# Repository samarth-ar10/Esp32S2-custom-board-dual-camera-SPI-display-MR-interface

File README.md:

# Esp32S2-custom-board-dual-camera-SPI-display-MR-interface

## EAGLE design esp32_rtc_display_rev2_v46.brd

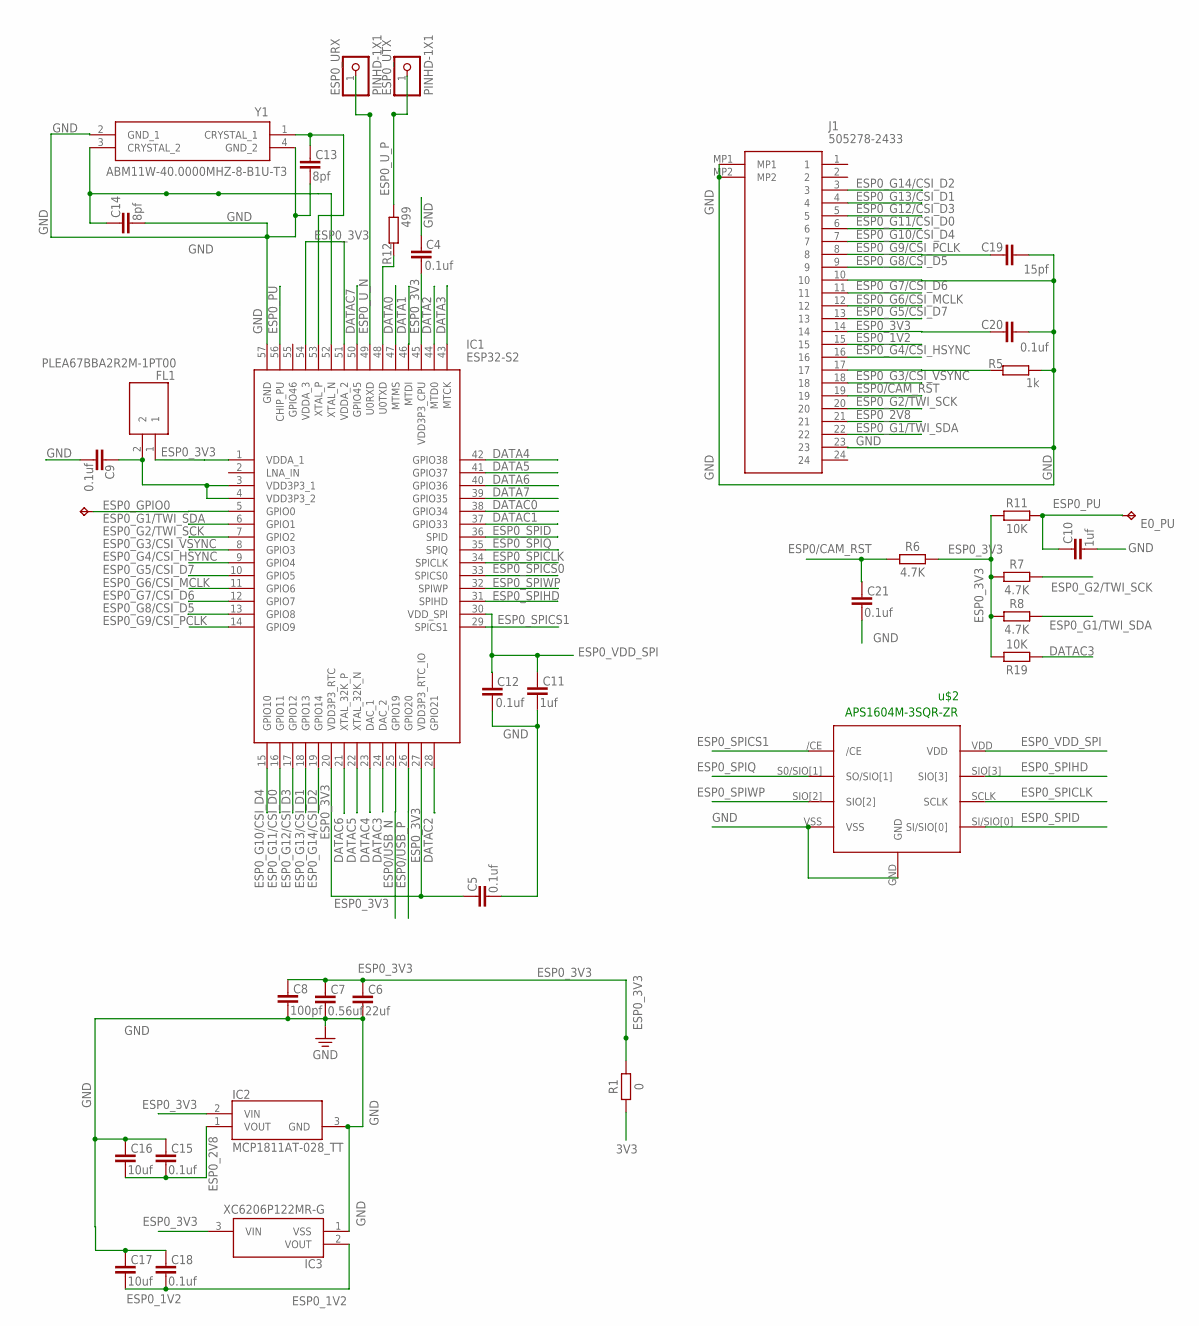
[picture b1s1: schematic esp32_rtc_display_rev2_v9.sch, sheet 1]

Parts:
C4, C5, C9, C12, C15, C18, C20, C21: 0.1uf; CAPC1005X60
C6: 22uf; CAPC1005X60
C7: 0.56uf; CAPC1005X60
C8: 100pf; CAPC1005X60
C10, C11: 1uf; CAPC1005X60
C13, C14: 8pf; CAPC1005X60
C16, C17: 10uf; CAPC1005X60
C19: 15pf; CAPC1005X60
E0_G0, E0_PU: TPTP10R; TP10R
ESP0_URX, ESP0_UTX: PINHD-1X1; 1X01
FL1: PLEA67BBA2R2M-1PT00; PLEA67BBA2R2M1PT00
IC1: ESP32-S2; QFN40P700X700X90-57N
IC2: MCP1811AT-028_TT; SOT65P210X110-3N
IC3: XC6206P122MR-G; SOT95P280X130-3N
J1: 505278-2433; 5052782433
R1: 0; RESC1005X40
R5: 1k; RESC1005X40
R6, R7, R8: 4.7K; RESC1005X40
R11, R19: 10K; RESC1005X40
R12: 499; RESC1005X40
U$2: APS1604M-3SQR-ZR
Y1: ABM11W-40.0000MHZ-8-B1U-T3; ABM11W400000MHZ8B1UT3

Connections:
3V3: R1.2; also elsewhere on the board
DATA0: IC1.47 (MTMS); also elsewhere on the board
DATA1: IC1.46 (MTDI); also elsewhere on the board
DATA2: IC1.44 (MTD0); also elsewhere on the board
DATA3: IC1.43 (MTCK); also elsewhere on the board
DATA4: IC1.42 (GPIO38); also elsewhere on the board
DATA5: IC1.41 (GPIO37); also elsewhere on the board
DATA6: IC1.40 (GPIO36); also elsewhere on the board
DATA7: IC1.39 (GPIO35); also elsewhere on the board
DATAC0: IC1.38 (GPIO34); also elsewhere on the board
DATAC1: IC1.37 (GPIO33); also elsewhere on the board
DATAC2: IC1.28 (GPIO21); also elsewhere on the board
DATAC3: IC1.24 (DAC_2), R19.2; also elsewhere on the board
DATAC4: IC1.23 (DAC_1); also elsewhere on the board
DATAC5: IC1.22 (XTAL_32K_N); also elsewhere on the board
DATAC6: IC1.21 (XTAL_32K_P); also elsewhere on the board
DATAC7: IC1.50 (GPIO45); also elsewhere on the board
ESP0/CAM_RST: C21.1, J1.19, R6.1
ESP0/USB_N: IC1.25 (GPIO19); also elsewhere on the board
ESP0/USB_P: IC1.26 (GPIO20); also elsewhere on the board
ESP0_1V2: C17.2, C18.2, IC3.2 (VOUT), J1.15
ESP0_2V8: C15.2, C16.2, IC2.1 (VOUT), J1.21
ESP0_3V3: C4.2, C5.1, C6.1, C7.1, C8.1, C20.1, FL1.1, IC1.1 (VDDA_1), IC1.20 (VDD3P3_RTC), IC1.27 (VDD3P3_RTC_IO), IC1.45 (VDD3P3_CPU), IC1.51 (VDDA_2), IC1.54 (VDDA_3), IC2.2 (VIN), IC3.3 (VIN), J1.14, R1.1, R6.2, R7.2, R8.2, R11.2, R19.1
ESP0_G1/TWI_SDA: IC1.6 (GPIO1), J1.22, R8.1
ESP0_G2/TWI_SCK: IC1.7 (GPIO2), J1.20, R7.1
ESP0_G3/CSI_VSYNC: IC1.8 (GPIO3), J1.18
ESP0_G4/CSI_HSYNC: IC1.9 (GPIO4), J1.16
ESP0_G5/CSI_D7: IC1.10 (GPIO5), J1.13
ESP0_G6/CSI_MCLK: IC1.11 (GPIO6), J1.12
ESP0_G7/CSI_D6: IC1.12 (GPIO7), J1.11
ESP0_G8/CSI_D5: IC1.13 (GPIO8), J1.9
ESP0_G9/CSI_PCLK: C19.1, IC1.14 (GPIO9), J1.8
ESP0_G10/CSI_D4: IC1.15 (GPIO10), J1.7
ESP0_G11/CSI_D0: IC1.16 (GPIO11), J1.6
ESP0_G12/CSI_D3: IC1.17 (GPIO12), J1.5
ESP0_G13/CSI_D1: IC1.18 (GPIO13), J1.4
ESP0_G14/CSI_D2: IC1.19 (GPIO14), J1.3
ESP0_GPIO0: E0_G0.TP, IC1.5 (GPIO0); also elsewhere on the board
ESP0_PU: C10.1, E0_PU.TP, IC1.56 (CHIP_PU), R11.1; also elsewhere on the board
ESP0_SPICLK: IC1.34 (SPICLK), U$2.SCLK
ESP0_SPICS0: IC1.33 (SPICS0)
ESP0_SPICS1: IC1.29 (SPICS1), U$2./CE
ESP0_SPID: IC1.36 (SPID), U$2.SI/SIO[0]
ESP0_SPIHD: IC1.31 (SPIHD), U$2.SIO[3]
ESP0_SPIQ: IC1.35 (SPIQ), U$2.S0/SIO[1] (SO/SIO[1])
ESP0_SPIWP: IC1.32 (SPIWP), U$2.SIO[2]
ESP0_U_N: ESP0_URX.1, IC1.49 (U0RXD); also elsewhere on the board
ESP0_U_P: ESP0_UTX.1, R12.2; also elsewhere on the board
ESP0_VDD_SPI: C11.1, C12.1, IC1.30 (VDD_SPI), U$2.VDD
GND: C4.1, C5.2, C6.2, C7.2, C8.2, C9.2, C10.2, C11.2, C12.2, C13.2, C14.2, C15.1, C16.1, C17.1, C18.1, C19.2, C20.2, C21.2, IC1.57 (GND), IC2.3 (GND), IC3.1 (VSS), J1.10, J1.23, J1.MP1, J1.MP2, R5.2, U$2.GND, U$2.VSS, Y1.2 (GND_1), Y1.4 (GND_2); also elsewhere on the board
unnamed: C13.1, IC1.53 (XTAL_P), Y1.1 (CRYSTAL_1)
unnamed: IC1.48 (U0TXD), R12.1
unnamed: C14.1, IC1.52 (XTAL_N), Y1.3 (CRYSTAL_2)
unnamed: J1.17, R5.1
unnamed: C9.1, FL1.2, IC1.3 (VDD3P3_1), IC1.4 (VDD3P3_2)

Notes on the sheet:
APS1604M-3SQR-ZR
u$2

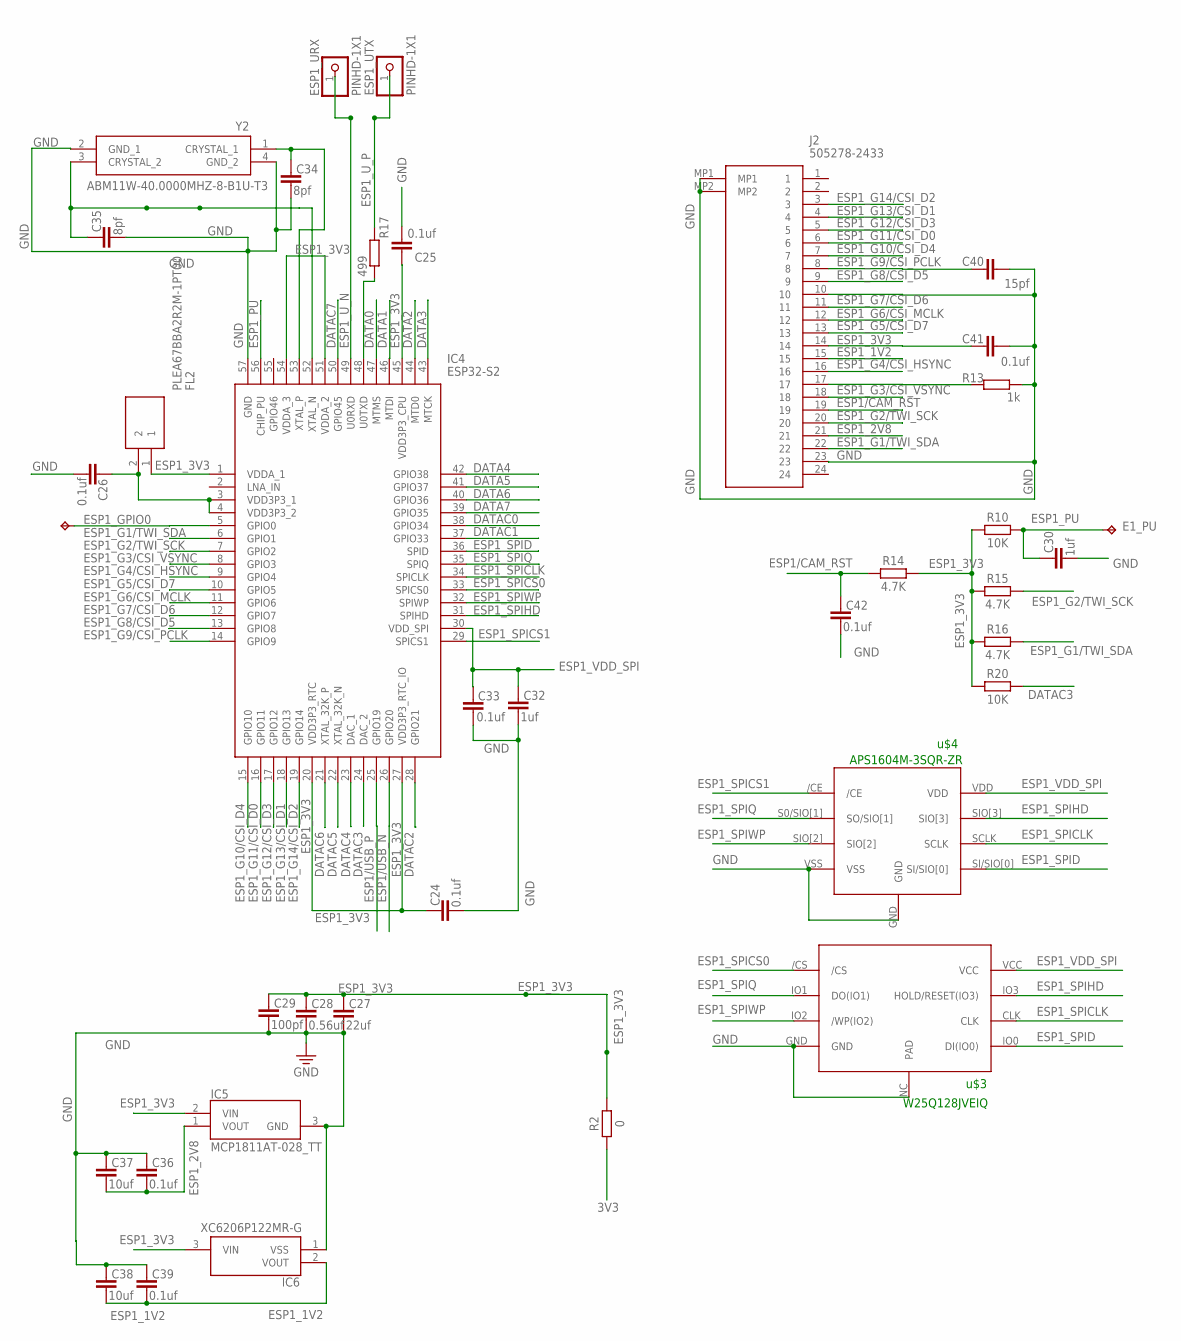
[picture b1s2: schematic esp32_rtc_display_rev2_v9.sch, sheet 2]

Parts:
C24, C25, C26, C33, C36, C39, C41, C42: 0.1uf; CAPC1005X60
C27: 22uf; CAPC1005X60
C28: 0.56uf; CAPC1005X60
C29: 100pf; CAPC1005X60
C30, C32: 1uf; CAPC1005X60
C34, C35: 8pf; CAPC1005X60
C37, C38: 10uf; CAPC1005X60
C40: 15pf; CAPC1005X60
E1_G0, E1_PU: TPTP10R; TP10R
ESP1_URX, ESP1_UTX: PINHD-1X1; 1X01
FL2: PLEA67BBA2R2M-1PT00; PLEA67BBA2R2M1PT00
IC4: ESP32-S2; QFN40P700X700X90-57N
IC5: MCP1811AT-028_TT; SOT65P210X110-3N
IC6: XC6206P122MR-G; SOT95P280X130-3N
J2: 505278-2433; 5052782433
R2: 0; RESC1005X40
R10, R20: 10K; RESC1005X40
R13: 1k; RESC1005X40
R14, R15, R16: 4.7K; RESC1005X40
R17: 499; RESC1005X40
U$3: W25Q128JVEIQ
U$4: APS1604M-3SQR-ZR
Y2: ABM11W-40.0000MHZ-8-B1U-T3; ABM11W400000MHZ8B1UT3

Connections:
3V3: R2.2; also elsewhere on the board
DATA0: IC4.47 (MTMS); also elsewhere on the board
DATA1: IC4.46 (MTDI); also elsewhere on the board
DATA2: IC4.44 (MTD0); also elsewhere on the board
DATA3: IC4.43 (MTCK); also elsewhere on the board
DATA4: IC4.42 (GPIO38); also elsewhere on the board
DATA5: IC4.41 (GPIO37); also elsewhere on the board
DATA6: IC4.40 (GPIO36); also elsewhere on the board
DATA7: IC4.39 (GPIO35); also elsewhere on the board
DATAC0: IC4.38 (GPIO34); also elsewhere on the board
DATAC1: IC4.37 (GPIO33); also elsewhere on the board
DATAC2: IC4.28 (GPIO21); also elsewhere on the board
DATAC3: IC4.24 (DAC_2), R20.1; also elsewhere on the board
DATAC4: IC4.23 (DAC_1); also elsewhere on the board
DATAC5: IC4.22 (XTAL_32K_N); also elsewhere on the board
DATAC6: IC4.21 (XTAL_32K_P); also elsewhere on the board
DATAC7: IC4.50 (GPIO45); also elsewhere on the board
ESP1/CAM_RST: C42.1, J2.19, R14.1
ESP1/USB_N: IC4.26 (GPIO20); also elsewhere on the board
ESP1/USB_P: IC4.25 (GPIO19); also elsewhere on the board
ESP1_1V2: C38.2, C39.2, IC6.2 (VOUT), J2.15
ESP1_2V8: C36.2, C37.2, IC5.1 (VOUT), J2.21
ESP1_3V3: C24.1, C25.1, C27.1, C28.1, C29.1, C41.1, FL2.1, IC4.1 (VDDA_1), IC4.20 (VDD3P3_RTC), IC4.27 (VDD3P3_RTC_IO), IC4.45 (VDD3P3_CPU), IC4.51 (VDDA_2), IC4.54 (VDDA_3), IC5.2 (VIN), IC6.3 (VIN), J2.14, R2.1, R10.2, R14.2, R15.2, R16.2, R20.2
ESP1_G1/TWI_SDA: IC4.6 (GPIO1), J2.22, R16.1
ESP1_G2/TWI_SCK: IC4.7 (GPIO2), J2.20, R15.1
ESP1_G3/CSI_VSYNC: IC4.8 (GPIO3), J2.18
ESP1_G4/CSI_HSYNC: IC4.9 (GPIO4), J2.16
ESP1_G5/CSI_D7: IC4.10 (GPIO5), J2.13
ESP1_G6/CSI_MCLK: IC4.11 (GPIO6), J2.12
ESP1_G7/CSI_D6: IC4.12 (GPIO7), J2.11
ESP1_G8/CSI_D5: IC4.13 (GPIO8), J2.9
ESP1_G9/CSI_PCLK: C40.1, IC4.14 (GPIO9), J2.8
ESP1_G10/CSI_D4: IC4.15 (GPIO10), J2.7
ESP1_G11/CSI_D0: IC4.16 (GPIO11), J2.6
ESP1_G12/CSI_D3: IC4.17 (GPIO12), J2.5
ESP1_G13/CSI_D1: IC4.18 (GPIO13), J2.4
ESP1_G14/CSI_D2: IC4.19 (GPIO14), J2.3
ESP1_GPIO0: E1_G0.TP, IC4.5 (GPIO0); also elsewhere on the board
ESP1_PU: C30.1, E1_PU.TP, IC4.56 (CHIP_PU), R10.1; also elsewhere on the board
ESP1_SPICLK: IC4.34 (SPICLK), U$3.CLK, U$4.SCLK
ESP1_SPICS0: IC4.33 (SPICS0), U$3./CS
ESP1_SPICS1: IC4.29 (SPICS1), U$4./CE
ESP1_SPID: IC4.36 (SPID), U$3.IO0 (DI(IO0)), U$4.SI/SIO[0]
ESP1_SPIHD: IC4.31 (SPIHD), U$3.IO3 (HOLD/RESET(IO3)), U$4.SIO[3]
ESP1_SPIQ: IC4.35 (SPIQ), U$3.IO1 (DO(IO1)), U$4.S0/SIO[1] (SO/SIO[1])
ESP1_SPIWP: IC4.32 (SPIWP), U$3.IO2 (/WP(IO2)), U$4.SIO[2]
ESP1_U_N: ESP1_URX.1, IC4.49 (U0RXD); also elsewhere on the board
ESP1_U_P: ESP1_UTX.1, R17.1; also elsewhere on the board
ESP1_VDD_SPI: C32.1, C33.1, IC4.30 (VDD_SPI), U$3.VCC, U$4.VDD
GND: C24.2, C25.2, C26.2, C27.2, C28.2, C29.2, C30.2, C32.2, C33.2, C34.2, C35.2, C36.1, C37.1, C38.1, C39.1, C40.2, C41.2, C42.2, IC4.57 (GND), IC5.3 (GND), IC6.1 (VSS), J2.10, J2.23, J2.MP1, J2.MP2, R13.2, U$3.GND, U$3.NC (PAD), U$4.GND, U$4.VSS, Y2.2 (GND_1), Y2.4 (GND_2); also elsewhere on the board
unnamed: IC4.48 (U0TXD), R17.2
unnamed: C35.1, IC4.52 (XTAL_N), Y2.3 (CRYSTAL_2)
unnamed: C34.1, IC4.53 (XTAL_P), Y2.1 (CRYSTAL_1)
unnamed: J2.17, R13.1
unnamed: C26.1, FL2.2, IC4.3 (VDD3P3_1), IC4.4 (VDD3P3_2)

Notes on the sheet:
APS1604M-3SQR-ZR
u$4
W25Q128JVEIQ
u$3

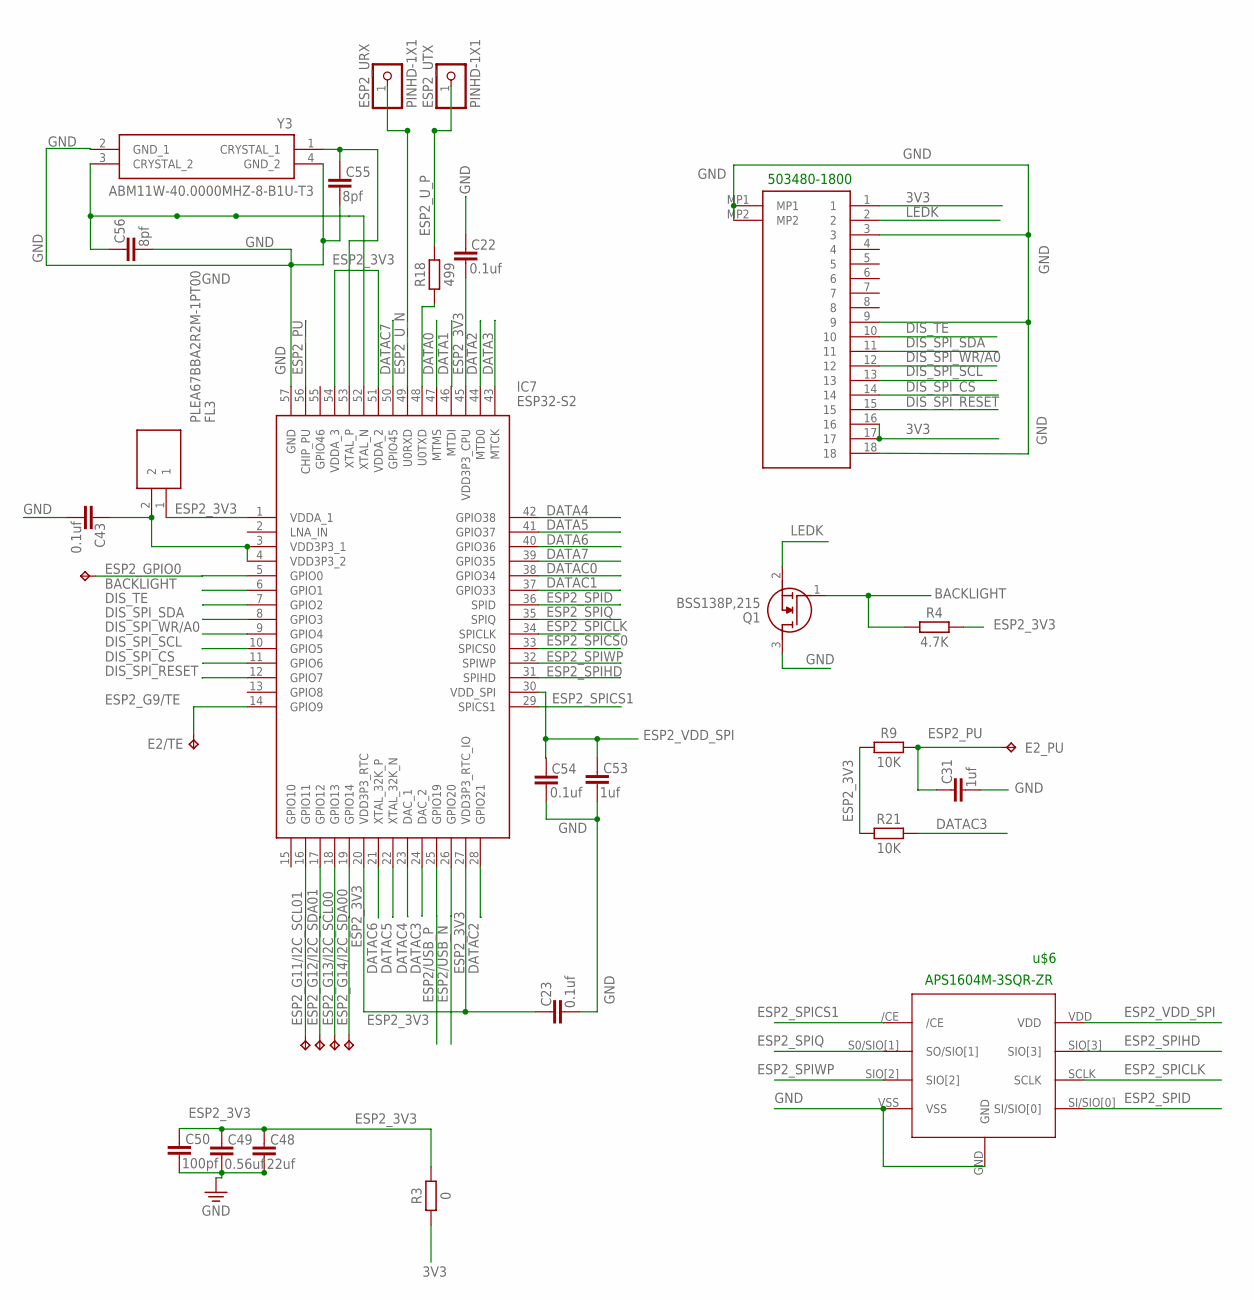
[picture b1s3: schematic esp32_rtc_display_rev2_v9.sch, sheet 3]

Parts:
C22, C23, C43, C54: 0.1uf; CAPC1005X60
C31, C53: 1uf; CAPC1005X60
C48: 22uf; CAPC1005X60
C49: 0.56uf; CAPC1005X60
C50: 100pf; CAPC1005X60
C55, C56: 8pf; CAPC1005X60
E2/TE, E2_G0, E2_PU: TPTP10R; TP10R
ESP2_URX, ESP2_UTX: PINHD-1X1; 1X01
FL3: PLEA67BBA2R2M-1PT00; PLEA67BBA2R2M1PT00
IC7: ESP32-S2; QFN40P700X700X90-57N
Q1: BSS138P,215; SOT95P230X110-3N
R3: 0; RESC1005X40
R4: 4.7K; RESC1005X40
R9, R21: 10K; RESC1005X40
R18: 499; RESC1005X40
SCL00, SCL01: TPTP10R; TP10R
SDA00, SDA01: TPTP10R; TP10R
U$5: 503480-1800; 5034801800
U$6: APS1604M-3SQR-ZR
Y3: ABM11W-40.0000MHZ-8-B1U-T3; ABM11W400000MHZ8B1UT3

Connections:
3V3: R3.2, U$5.1, U$5.16, U$5.17; also elsewhere on the board
BACKLIGHT: IC7.6 (GPIO1), Q1.1 (G), R4.1
DATA0: IC7.47 (MTMS); also elsewhere on the board
DATA1: IC7.46 (MTDI); also elsewhere on the board
DATA2: IC7.44 (MTD0); also elsewhere on the board
DATA3: IC7.43 (MTCK); also elsewhere on the board
DATA4: IC7.42 (GPIO38); also elsewhere on the board
DATA5: IC7.41 (GPIO37); also elsewhere on the board
DATA6: IC7.40 (GPIO36); also elsewhere on the board
DATA7: IC7.39 (GPIO35); also elsewhere on the board
DATAC0: IC7.38 (GPIO34); also elsewhere on the board
DATAC1: IC7.37 (GPIO33); also elsewhere on the board
DATAC2: IC7.28 (GPIO21); also elsewhere on the board
DATAC3: IC7.24 (DAC_2), R21.1; also elsewhere on the board
DATAC4: IC7.23 (DAC_1); also elsewhere on the board
DATAC5: IC7.22 (XTAL_32K_N); also elsewhere on the board
DATAC6: IC7.21 (XTAL_32K_P); also elsewhere on the board
DATAC7: IC7.50 (GPIO45); also elsewhere on the board
DIS_SPI_CS: IC7.11 (GPIO6), U$5.14
DIS_SPI_RESET: IC7.12 (GPIO7), U$5.15
DIS_SPI_SCL: IC7.10 (GPIO5), U$5.13
DIS_SPI_SDA: IC7.8 (GPIO3), U$5.11
DIS_SPI_WR/A0: IC7.9 (GPIO4), U$5.12
DIS_TE: IC7.7 (GPIO2), U$5.10
ESP2/USB_N: IC7.26 (GPIO20); also elsewhere on the board
ESP2/USB_P: IC7.25 (GPIO19); also elsewhere on the board
ESP2_3V3: C22.2, C23.1, C48.1, C49.1, C50.1, FL3.1, IC7.1 (VDDA_1), IC7.20 (VDD3P3_RTC), IC7.27 (VDD3P3_RTC_IO), IC7.45 (VDD3P3_CPU), IC7.51 (VDDA_2), IC7.54 (VDDA_3), R3.1, R4.2, R9.2, R21.2
ESP2_G9/TE: E2/TE.TP, IC7.14 (GPIO9)
ESP2_G11/I2C_SCL01: IC7.16 (GPIO11), SCL01.TP
ESP2_G12/I2C_SDA01: IC7.17 (GPIO12), SDA01.TP
ESP2_G13/I2C_SCL00: IC7.18 (GPIO13), SCL00.TP
ESP2_G14/I2C_SDA00: IC7.19 (GPIO14), SDA00.TP
ESP2_GPIO0: E2_G0.TP, IC7.5 (GPIO0); also elsewhere on the board
ESP2_PU: C31.1, E2_PU.TP, IC7.56 (CHIP_PU), R9.1; also elsewhere on the board
ESP2_SPICLK: IC7.34 (SPICLK), U$6.SCLK
ESP2_SPICS0: IC7.33 (SPICS0)
ESP2_SPICS1: IC7.29 (SPICS1), U$6./CE
ESP2_SPID: IC7.36 (SPID), U$6.SI/SIO[0]
ESP2_SPIHD: IC7.31 (SPIHD), U$6.SIO[3]
ESP2_SPIQ: IC7.35 (SPIQ), U$6.S0/SIO[1] (SO/SIO[1])
ESP2_SPIWP: IC7.32 (SPIWP), U$6.SIO[2]
ESP2_U_N: ESP2_URX.1, IC7.49 (U0RXD); also elsewhere on the board
ESP2_U_P: ESP2_UTX.1, R18.2; also elsewhere on the board
ESP2_VDD_SPI: C53.1, C54.1, IC7.30 (VDD_SPI), U$6.VDD
GND: C22.1, C23.2, C31.2, C43.2, C48.2, C49.2, C50.2, C53.2, C54.2, C55.2, C56.2, IC7.57 (GND), Q1.3 (D), U$5.3, U$5.9, U$5.18, U$5.MP1, U$5.MP2, U$6.GND, U$6.VSS, Y3.2 (GND_1), Y3.4 (GND_2); also elsewhere on the board
LEDK: Q1.2 (S), U$5.2
unnamed: C56.1, IC7.52 (XTAL_N), Y3.3 (CRYSTAL_2)
unnamed: C55.1, IC7.53 (XTAL_P), Y3.1 (CRYSTAL_1)
unnamed: IC7.48 (U0TXD), R18.1
unnamed: C43.1, FL3.2, IC7.3 (VDD3P3_1), IC7.4 (VDD3P3_2)

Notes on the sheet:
APS1604M-3SQR-ZR
u$6
503480-1800

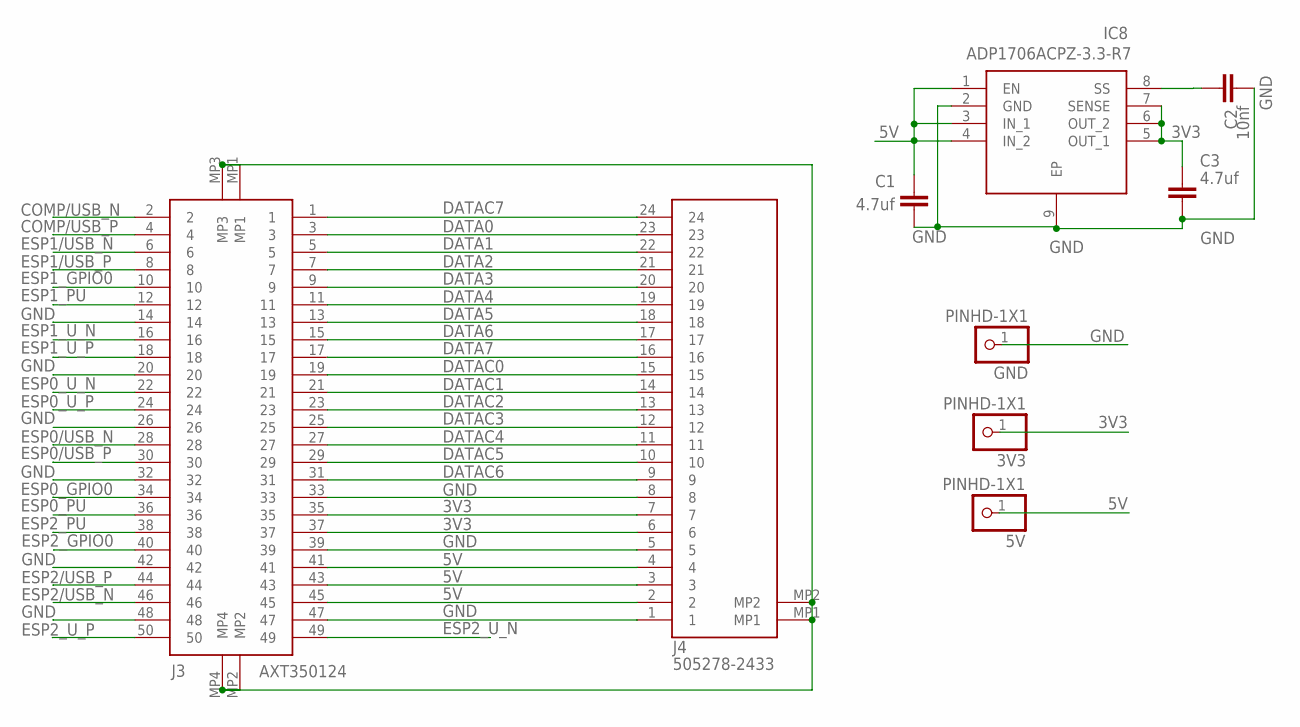
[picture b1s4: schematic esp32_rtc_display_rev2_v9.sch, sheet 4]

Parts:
3V3, 5V: PINHD-1X1; 1X01
C1, C3: 4.7uf; CAPC1005X60
C2: 10nf; CAPC1005X60
GND: PINHD-1X1; 1X01
IC8: ADP1706ACPZ-3.3-R7; SON50P300X300X80-9N
J3: AXT350124
J4: 505278-2433; 5052782433

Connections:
3V3: 3V3.1, C3.1, IC8.5 (OUT_1), IC8.6 (OUT_2), IC8.7 (SENSE), J3.35, J3.37, J4.6, J4.7; also elsewhere on the board
5V: 5V.1, C1.1, IC8.1 (EN), IC8.3 (IN_1), IC8.4 (IN_2), J3.41, J3.43, J3.45, J4.2, J4.3, J4.4
COMP/USB_N: J3.2
COMP/USB_P: J3.4
DATA0: J3.3, J4.23; also elsewhere on the board
DATA1: J3.5, J4.22; also elsewhere on the board
DATA2: J3.7, J4.21; also elsewhere on the board
DATA3: J3.9, J4.20; also elsewhere on the board
DATA4: J3.11, J4.19; also elsewhere on the board
DATA5: J3.13, J4.18; also elsewhere on the board
DATA6: J3.15, J4.17; also elsewhere on the board
DATA7: J3.17, J4.16; also elsewhere on the board
DATAC0: J3.19, J4.15; also elsewhere on the board
DATAC1: J3.21, J4.14; also elsewhere on the board
DATAC2: J3.23, J4.13; also elsewhere on the board
DATAC3: J3.25, J4.12; also elsewhere on the board
DATAC4: J3.27, J4.11; also elsewhere on the board
DATAC5: J3.29, J4.10; also elsewhere on the board
DATAC6: J3.31, J4.9; also elsewhere on the board
DATAC7: J3.1, J4.24; also elsewhere on the board
ESP0/USB_N: J3.28; also elsewhere on the board
ESP0/USB_P: J3.30; also elsewhere on the board
ESP0_GPIO0: J3.34; also elsewhere on the board
ESP0_PU: J3.36; also elsewhere on the board
ESP0_U_N: J3.22; also elsewhere on the board
ESP0_U_P: J3.24; also elsewhere on the board
ESP1/USB_N: J3.6; also elsewhere on the board
ESP1/USB_P: J3.8; also elsewhere on the board
ESP1_GPIO0: J3.10; also elsewhere on the board
ESP1_PU: J3.12; also elsewhere on the board
ESP1_U_N: J3.16; also elsewhere on the board
ESP1_U_P: J3.18; also elsewhere on the board
ESP2/USB_N: J3.46; also elsewhere on the board
ESP2/USB_P: J3.44; also elsewhere on the board
ESP2_GPIO0: J3.40; also elsewhere on the board
ESP2_PU: J3.38; also elsewhere on the board
ESP2_U_N: J3.49; also elsewhere on the board
ESP2_U_P: J3.50; also elsewhere on the board
GND: C1.2, C2.1, C3.2, GND.1, IC8.2 (GND), IC8.9 (EP), J3.14, J3.20, J3.26, J3.32, J3.33, J3.39, J3.42, J3.47, J3.48, J3.MP1, J3.MP2, J3.MP3, J3.MP4, J4.1, J4.5, J4.8, J4.MP1, J4.MP2; also elsewhere on the board
unnamed: C2.2, IC8.8 (SS)

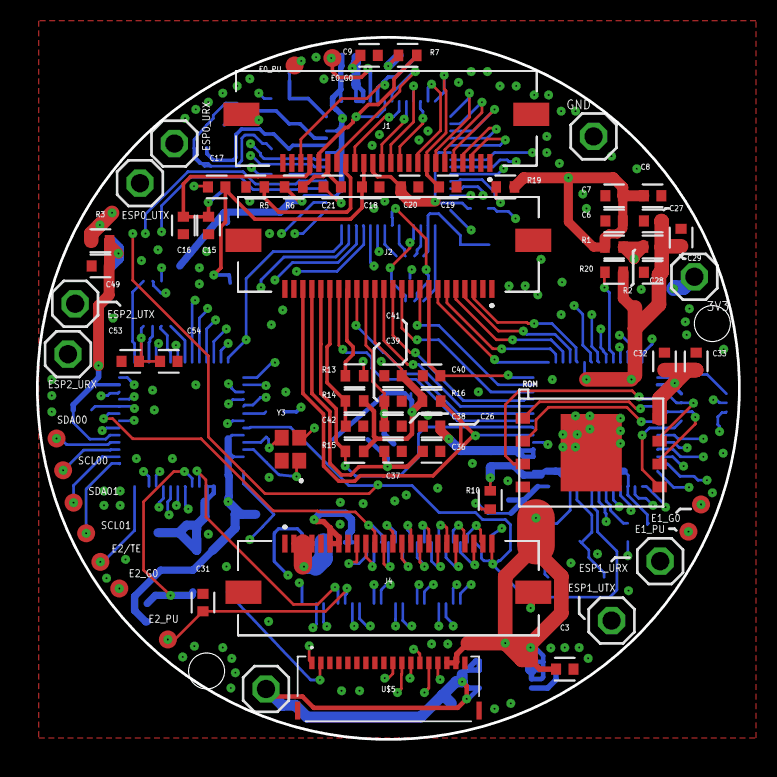
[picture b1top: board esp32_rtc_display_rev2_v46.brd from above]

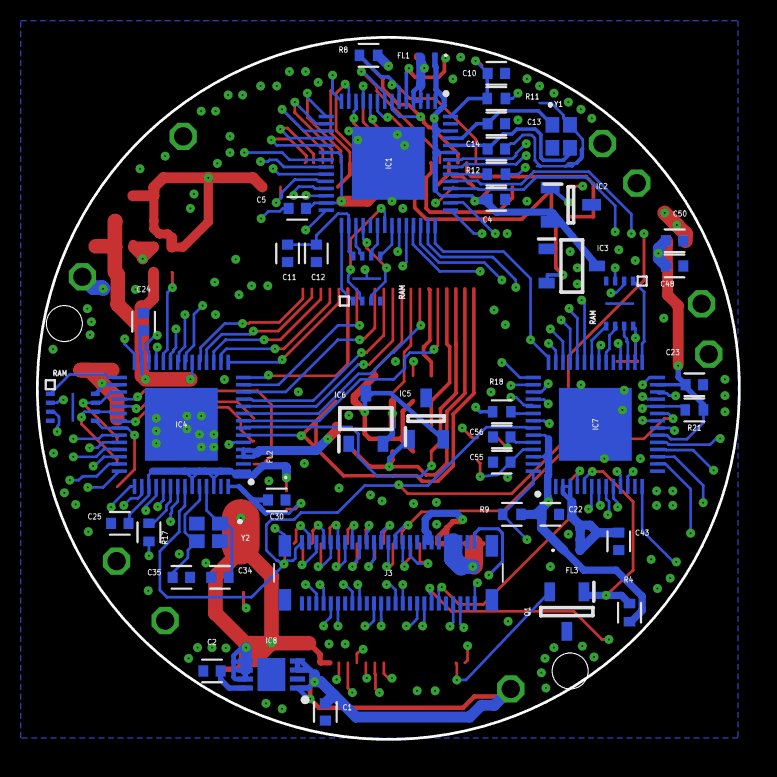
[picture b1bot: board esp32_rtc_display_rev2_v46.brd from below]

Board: 6 copper layers, 39.0 x 39.0 mm, 115 parts (47 on the bottom side), 124 nets.

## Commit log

2024-12-29 uploading schematic
2024-12-29 adding brd file
2024-12-29 adding the 3d file
2024-12-29 adding schematic pdf for better documentation and easy readability
